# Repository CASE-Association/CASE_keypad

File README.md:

# CASE keypad
2x3 Keypad kit

## Assembly instructions
This kit requires SMD soldering of 0805 components and a QFP microcontroller. [See this for quick guide in hand-soldering SMD components](https://www.youtube.com/watch?v=EW9Y8rDm4kE)
Recommended soldering order:
  - Diodes 
  - Resistors/Capacitors
  - Pushbutton
  - Microcontroller
  - USB-C 
  - Crystal 
  - Switches/Encoder (Test and flash before soldering!)

`Diodes have to be soldered in correct orientation. White line facing downwards.`

`Dot on microcontroller should align with white dot on PCB.`

Rest of the components can be soldered in arbitrary orientation.

The keypad can be tested and flashed after soldering the crystal.

 - Plug in to computer
 - Check device manager for ATmega32u2
 - Keypad is working and ready for flashing if ATmega32u2 is detected
 - Proceed to flashing

## Flashing
  - Download and open [QMK Toolbox](https://github.com/qmk/qmk_toolbox/releases)
  - Select the provided [.HEX file](https://github.com/CASE-Association/CASE_keypad/releases/download/keypad-release/case_keypad_via.hex) 
  - Choose ATMega32u2 as microcontroller
  - Push reset button on board and then press flash button in toolbox
  
Keypad should be flashed and ready to test. 
Use a jumper wire or tweezers to short the switch pins. 
The keypad should print numbers 1 to 6.

If flashing does not work, try using v0.0.21 of QMK toolbox 

You can now solder the switches/encoder. Encoder is optional and can only be soldered in either top corner (ONLY ONE).
  
## Keybinds
  - Download and install [VIA Configurator](https://github.com/the-via/releases/releases) (select .exe for windows)
  - Open VIA and go to File->Import Keymap
  - Select the file [via.json](https://github.com/CASE-Association/CASE_keypad/releases/download/keypad-release/via.json)
  - Plug in the keypad

The keybinds can now be configured.

## Troubleshooting
### Unknown USB device
This is a common problem. Plug in the keyboard and open the device manager. The keyboard should show up as ATmega32U2, if it instead shows up as unknown device, something is wrong. Follow these steps: 
 - Check that the USB-C connector has no shorts and all pads are connected. It can be good to retouch the connection even if no obvious problem can be found.
 - Do the same thing for the microcontroller chip. 
 - Also check that the resistors are soldered properly.
 - Check the rest of the components.

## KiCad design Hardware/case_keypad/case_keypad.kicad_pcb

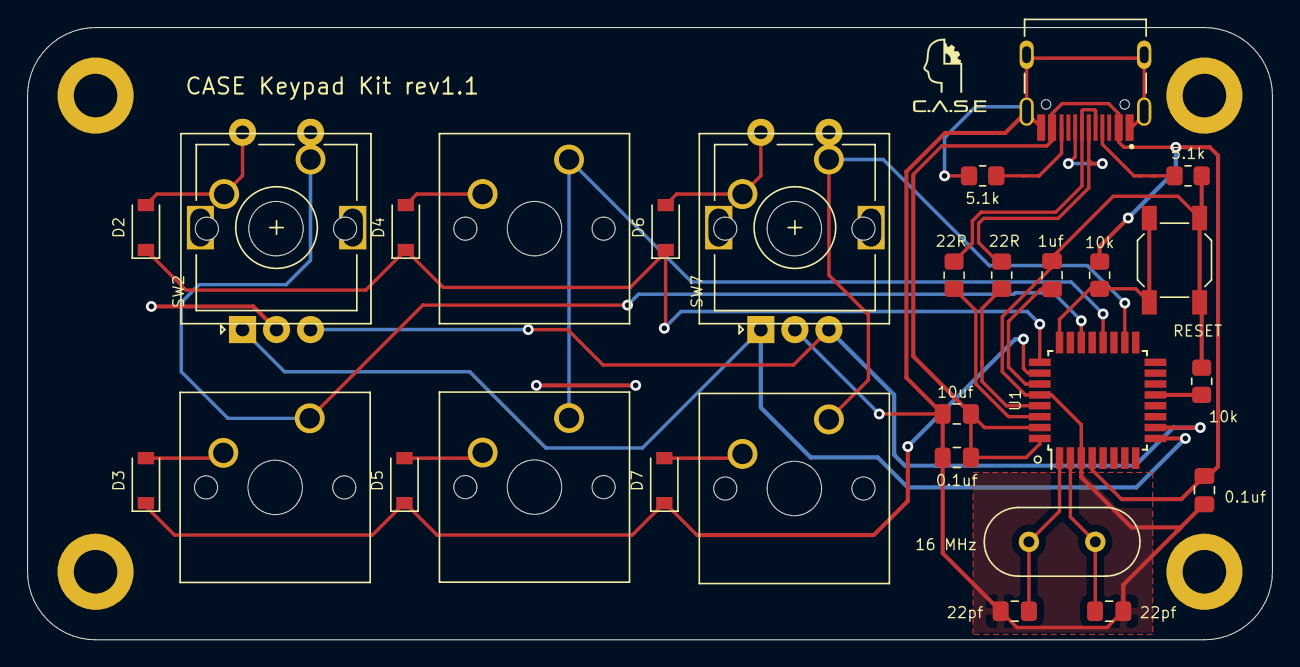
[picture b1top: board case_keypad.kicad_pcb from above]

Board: 2 copper layers, 91.5 x 45.0 mm, 30 parts (0 on the bottom side), 26 nets.

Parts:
0.1uf, 0.1uf#2: 0.1uF; C_0805_2012Metric_Pad1.18x1.45mm_HandSolder
1uf: 1uF; C_0805_2012Metric_Pad1.18x1.45mm_HandSolder
5.1k, 5.1k#2: 5.1k; R_0805_2012Metric_Pad1.20x1.40mm_HandSolder
10k, 10k#2: 10k; R_0805_2012Metric_Pad1.20x1.40mm_HandSolder
10uf: 10uF; C_0805_2012Metric_Pad1.18x1.45mm_HandSolder
16 MHz: 16 MHz; Crystal_HC49-4H_Vertical
22R, 22R#2: 22R; R_0805_2012Metric_Pad1.20x1.40mm_HandSolder
22pf, 22pf#2: 22 pF; C_0805_2012Metric_Pad1.18x1.45mm_HandSolder
D2, D3, D4, D5, D6, D7: D_Small; D_SOD-123
J1: TYPE-C-31-M-12; HRO_TYPE-C-31-M-12
RESET: RESET; SW_SPST_SKQG_WithStem
SW2, SW7: Encoder; RotaryEncoder_Alps_EC11E-Switch_Vertical_H20mm
SW3, SW4, SW5, SW6, SW8, SW9: SW_KEYSW; SW_Cherry_MX_1.00u_PCB
U1: ATmega32U2-AU; TQFP-32_7x7mm_P0.8mm

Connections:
+5V: 0.1uf.1, 0.1uf#2.1, 10k#2.2, 10uf.1, J1.A4B9, J1.B4A9, U1.4, U1.31, U1.32
A1: SW2.A, SW7.A, U1.9
B1: SW2.B, SW7.B, U1.10
D+: 22R#2.2, J1.A6, J1.B6
D-: 22R.2, J1.A7, J1.B7
GND: 0.1uf.2, 0.1uf#2.2, 1uf.2, 5.1k.2, 5.1k#2.2, 10k.1, 10uf.2, 22pf.2, 22pf#2.2, J1.A1B12, J1.B1A12, J1.S1, J1.S2, J1.S3, J1.S4, RESET.1, SW2.C, SW7.C, U1.3, U1.28
unnamed: 16 MHz.1, 22pf.1, U1.1
unnamed: 16 MHz.2, 22pf#2.1, U1.2
unnamed: 1uf.1, U1.27
unnamed: D2.2, SW2.S2, SW3.2
unnamed: D3.2, SW4.2
unnamed: D4.2, SW5.2
unnamed: D5.2, SW6.2
unnamed: D6.2, SW7.S2, SW8.2
unnamed: D7.2, SW9.2
unnamed: 5.1k.1, J1.A5
unnamed: 5.1k#2.1, J1.B5
unnamed: 22R#2.1, U1.29
unnamed: 22R.1, U1.30
unnamed: 10k#2.1, RESET.2, U1.24
unnamed: 10k.2, U1.13
col0: SW2.S1, SW3.1, SW4.1, U1.22
col1: SW5.1, SW6.1, U1.20
col2: SW7.S1, SW8.1, SW9.1, U1.18
row0: D2.1, D4.1, D6.1, U1.25
row1: D3.1, D5.1, D7.1, U1.26

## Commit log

2021-04-29 added img
2021-04-29 add software
2022-04-08 Create hardware folder
2022-04-08 Add knob
2022-09-15 Add links
2022-09-15 Add more links and troubleshooting
2022-10-10 add kicad files
